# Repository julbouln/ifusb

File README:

ifusb is a simple toolkit to access GPIO/UART/SPI/I2C from USB host through microcontroller.
It was initialy attended for use with eink controller project, but can be used as a tool for any project, like a Bus Pirate board or a FT2232 chip.

Firmware use libopencm3 and has been tested with STM32F042 microcontroller.
PR 663 is needed for I2C on STM32F0 https://github.com/libopencm3/libopencm3/pull/663
$ git fetch origin pull/663/head:pr-663
$ git checkout pr-663

Do not forget to edit OPENCM3_DIR in firmware/Makefine to your libopencm3 path.

Host library use libusb 1.0.

Finally, a reference design is available in hardware/ directory.

ifusb user access udev rules:
SUBSYSTEM=="usb", ATTR{idVendor}=="f055", ATTR{idProduct}=="cafe", MODE="0666"

TODO
- UART RX + MIN

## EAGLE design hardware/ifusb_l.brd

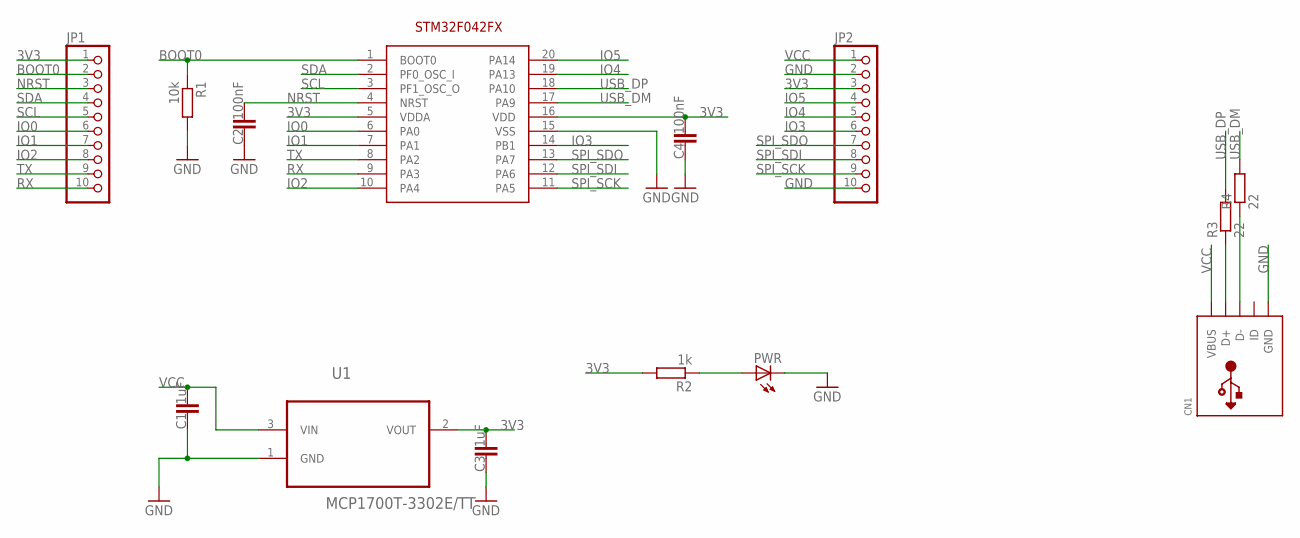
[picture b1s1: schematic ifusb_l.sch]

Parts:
C1, C3: 1uF; C0603K
C2, C4: 100nF; C0603K
CN1: USBMOLEX; USB-MINIB-THM-MOLEX
JP1, JP2: HEADER-1X10ROUND; 1X10_ROUND
PWR: LEDCHIP-LED0603; CHIP-LED0603
R1: 10k; R0603
R2: 1k; R0603
R3, R4: 22; R0603
U1: MCP1700T-3302E/TT; SOT95P237X112-3N
U2: STM32F042FX; TSSOP20

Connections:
3V3: C3.2, C4.2, JP1.1, JP2.3, R2.2, U1.2 (VOUT), U2.5 (VDDA), U2.16 (VDD)
BOOT0: JP1.2, R1.1, U2.1 (BOOT0)
GND: C1.1, C2.1, C3.1, C4.1, CN1.GND, JP2.2, JP2.10, PWR.C, R1.2, U1.1 (GND), U2.15 (VSS)
IO0: JP1.6, U2.6 (PA0)
IO1: JP1.7, U2.7 (PA1)
IO2: JP1.8, U2.10 (PA4)
IO3: JP2.6, U2.14 (PB1)
IO4: JP2.5, U2.19 (PA13)
IO5: JP2.4, U2.20 (PA14)
unnamed: CN1.D+, R3.1
unnamed: CN1.D-, R4.1
unnamed: PWR.A, R2.1
NRST: C2.2, JP1.3, U2.4 (NRST)
RX: JP1.10, U2.9 (PA3)
SCL: JP1.5, U2.3 (PF1_OSC_O)
SDA: JP1.4, U2.2 (PF0_OSC_I)
SPI_SCK: JP2.9, U2.11 (PA5)
SPI_SDI: JP2.8, U2.12 (PA6)
SPI_SDO: JP2.7, U2.13 (PA7)
TX: JP1.9, U2.8 (PA2)
USB_DM: R4.2, U2.17 (PA9)
USB_DP: R3.2, U2.18 (PA10)
VCC: C1.2, CN1.VBUS, JP2.1, U1.3 (VIN)

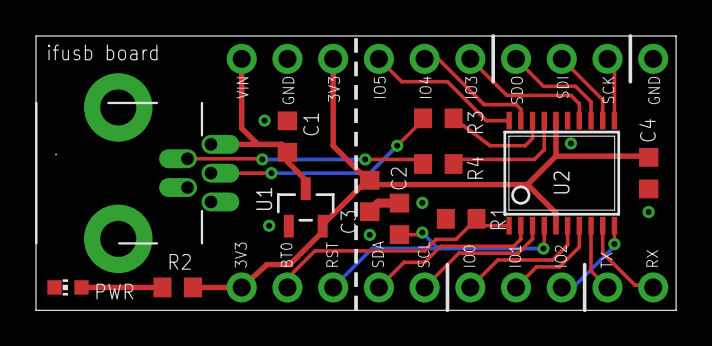
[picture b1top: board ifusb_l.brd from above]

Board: 2 copper layers, 35.6 x 15.2 mm, 14 parts (0 on the bottom side), 23 nets.

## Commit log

2017-04-13 initial input state for io pins
2017-04-15 add preliminary ruby binding
2017-04-15 add ruby blink simple test
2017-04-15 add sst25 flash iceprog for eink controller
2017-08-29 Make compatible with kitnic.it

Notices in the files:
parts and their libraries:
microbuilder: This work is placed in the public domain, and may be freely used for commercial and non-commercial work with the following conditions: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
